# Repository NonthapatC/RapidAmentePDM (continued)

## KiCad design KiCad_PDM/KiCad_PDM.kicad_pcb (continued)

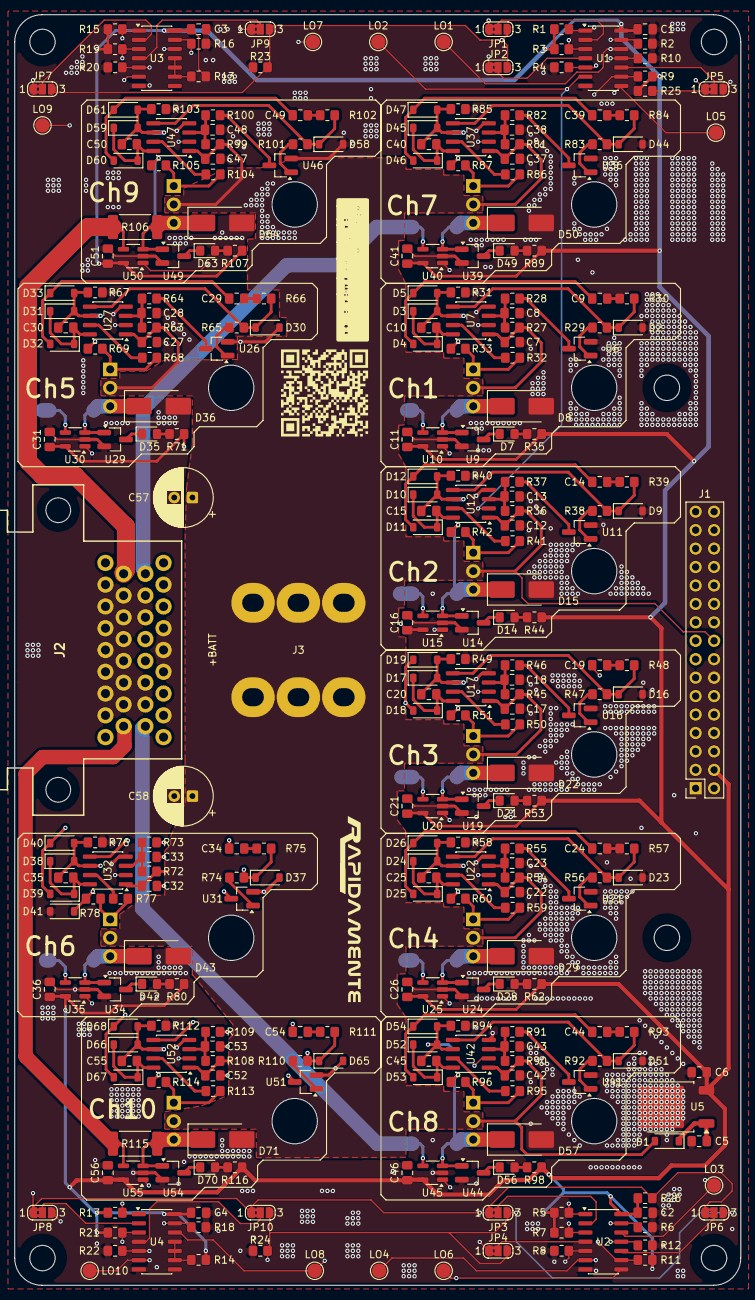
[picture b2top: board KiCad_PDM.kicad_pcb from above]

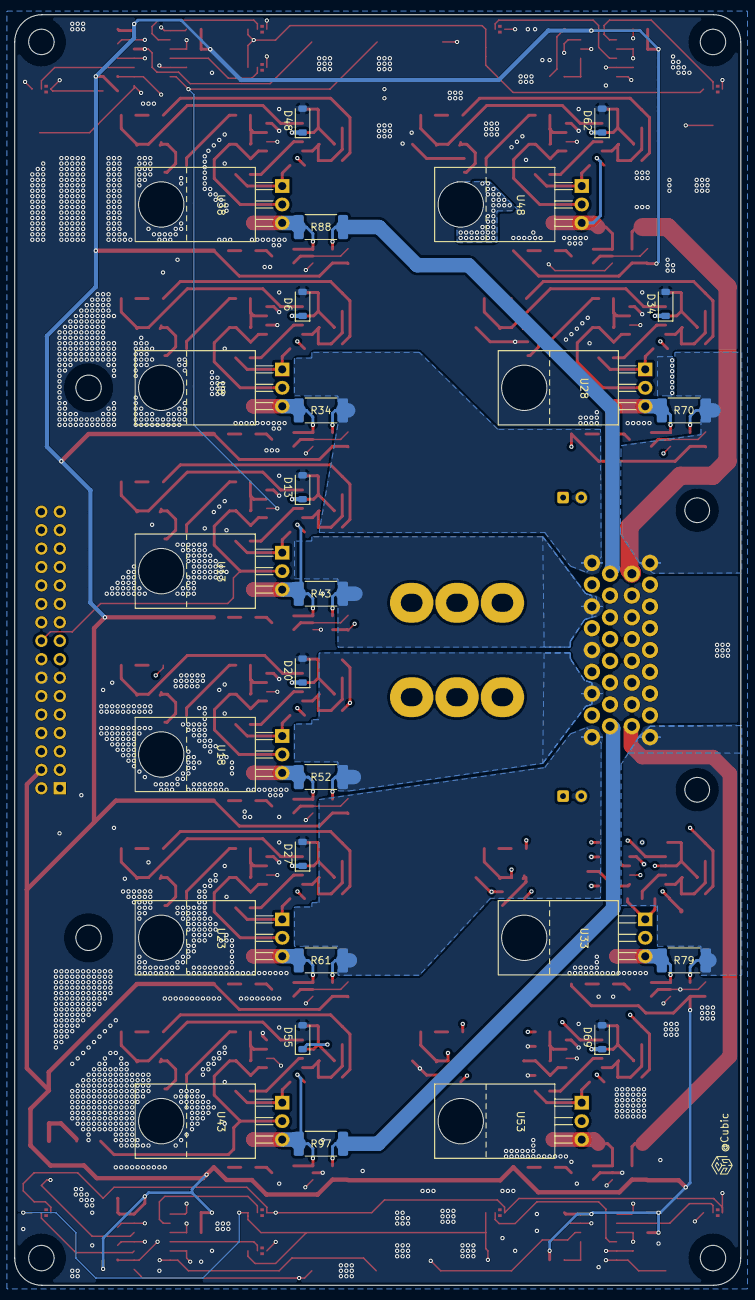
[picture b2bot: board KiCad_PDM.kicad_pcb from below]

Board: 4 copper layers, 100.0 x 175.0 mm, 329 parts (27 on the bottom side), 197 nets.

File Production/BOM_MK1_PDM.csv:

Reference,Qty,Value,LCSC part number,Datasheet
"C1,C2,C3,C4,C5,C11,C16,C21,C26,C31,C36,C41,C46,C51,C56",15,0.1uF,C1711,https://www.lcsc.com/product-detail/C1711.html
C6,1,2.2uF,C19110,https://www.lcsc.com/product-detail/C19110.html
"C7,C12,C17,C22,C27,C32,C37,C42,C47,C52",10,1uF,C116352,https://www.lcsc.com/product-detail/C116352.html
"C8,C13,C18,C23,C28,C33,C38,C43,C48,C53",10,2.2nF,C1728,https://www.lcsc.com/product-detail/C1728.html
"C9,C14,C19,C24,C29,C34,C39,C44,C49,C54",10,10nF,C106841,https://www.lcsc.com/product-detail/C106841.html
"C10,C15,C20,C25,C30,C35,C40,C45,C50,C55",10,1uF,C28323,https://www.lcsc.com/product-detail/C28323.html
"D1,D4,D5,D11,D12,D18,D19,D25,D26,D32,D33,D39,D40,D46,D47,D53,D54,D60,D61,D67,D68",21,FR107,C963379,https://www.lcsc.com/product-detail/C963379.html
"D2,D3,D9,D10,D16,D17,D23,D24,D30,D31,D37,D38,D44,D45,D51,D52,D58,D59,D65,D66",20,MMSZ47202T1G,C242274,https://www.lcsc.com/product-detail/C242274.html
"D6,D13,D20,D27,D34,D41,D48,D55,D62,D69",10,1N5819HW-7-F,C82544,https://www.lcsc.com/product-detail/C82544.html
"D7,D14,D21,D28,D35,D42,D49,D56,D63,D70",10,RLED,C965812,https://www.lcsc.com/product-detail/C965812.html
"D8,D15,D22,D29,D36,D43,D50,D57,D64,D71",10,SS1045-SMB,C2903947,https://www.lcsc.com/product-detail/C2903947.html
J1,1,Conn_02x16_Top_Bottom,C7499351,https://www.lcsc.com/product-detail/C7499351.html
J2,1,6437288-1,C574787,https://www.lcsc.com/product-detail/C574787.html
J3,1,T66145145-1500,C19724526,https://www.lcsc.com/product-detail/C19724526.html
"R1,R2,R3,R4,R5,R6,R7,R8,R9,R10,R11,R12,R13,R14,R15,R16,R17,R18,R19,R20,R21,R22,R23,R24,R25,R26",26,10K,C2907219,https://www.lcsc.com/product-detail/C2907219.html
"R27,R36,R45,R54,R63,R72,R81,R90,R99,R108",10,39K,C407451,https://www.lcsc.com/product-detail/C407451.html
"R28,R37,R46,R55,R64,R73,R82,R91,R100,R109",10,1K,C2907232,https://www.lcsc.com/product-detail/C2907232.html
"R29,R38,R47,R56,R65,R74,R83,R92,R101,R110",10,5.1K,C2907269,https://www.lcsc.com/product-detail/C2907269.html
"R30,R39,R48,R57,R66,R75,R84,R93,R102,R111",10,50,C2828866,https://www.lcsc.com/product-detail/C2828866.html
"R31,R40,R49,R58,R67,R76,R85,R94,R103,R112",10,500K,C3097783,https://www.lcsc.com/product-detail/C3097783.html
"R32,R41,R50,R59,R68,R77,R86,R95,R104,R113",10,430,C2907265,https://www.lcsc.com/product-detail/C2907265.html
"R33,R42,R51,R60,R69,R78,R87,R96,R105,R114",10,51K,C2933461,https://www.lcsc.com/product-detail/C2933461.html
"R34,R43,R52,R61,R70,R79,R88,R97,R106,R115",10,1m,C7467238,https://www.lcsc.com/product-detail/C7467238.html
"R35,R44,R53,R62,R71,R80,R89,R98,R107,R116",10,82,C2907287,https://www.lcsc.com/product-detail/C2907287.html
"U1,U2,U3,U4",4,74HC27D,C5629,https://www.lcsc.com/product-detail/C5629.html
U5,1,KF33BDT-TR,C283274,https://www.lcsc.com/product-detail/C283274.html
"U6,U9,U11,U14,U16,U19,U21,U24,U26,U29,U31,U34,U36,U39,U41,U44,U46,U49,U51,U54",20,2N7002,C65189,https://www.lcsc.com/product-detail/C65189.html
"U7,U12,U17,U22,U27,U32,U37,U42,U47,U52",10,NSG2000,C41414507,https://www.lcsc.com/product-detail/C41414507.html
"U8,U13,U18,U23,U28,U33,U38,U43,U48,U53",10,OSP80N03T,C20607812,https://www.lcsc.com/product-detail/C20607812.html
"U10,U15,U20,U25,U30,U35,U40,U45,U50,U55",10,INA180A3IDBVR,C122882,https://www.lcsc.com/product-detail/C122882.html

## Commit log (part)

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2026-04-13 layout and tracing
2026-04-13 design constraint STEP file
2026-04-14 silk screen changes(logos and qr codes)
2026-04-14 updated design and 3d models
2026-04-14 added bom, renamed step file
2026-04-20 updated footprint library
2026-04-20 added symbol library
2026-05-05 added control board kicad files
